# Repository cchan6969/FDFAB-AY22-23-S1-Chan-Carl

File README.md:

# FDFAB-AY22-23-S1-Chan-Carl

Project Webpage + Repository for the Elective Module Further Digital Fabrication and Prototyping Fundementals.

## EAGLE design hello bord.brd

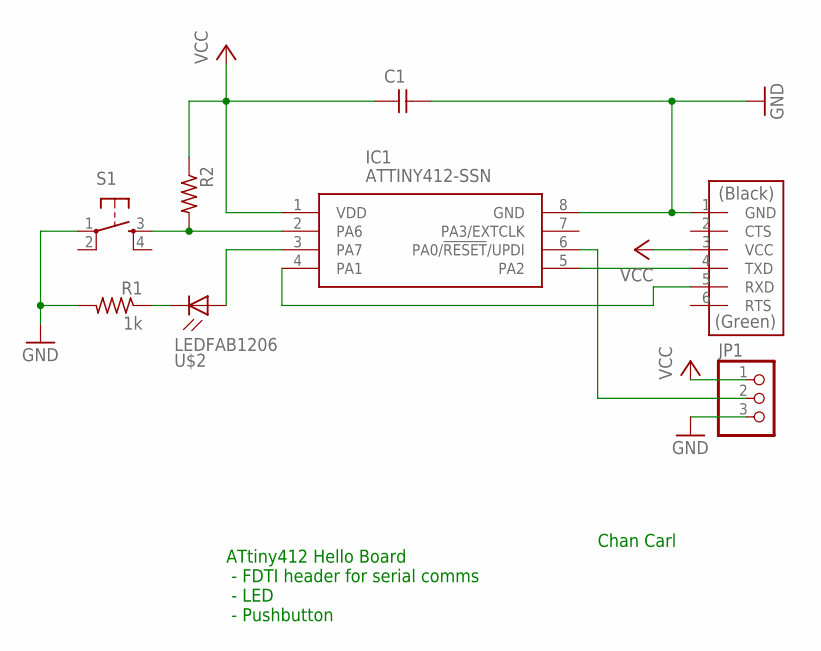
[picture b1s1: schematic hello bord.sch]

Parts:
C1: CAP_UNPOLARIZED; C1206
IC1: ATTINY412-SSN; SOIC127P600X175-8N
JP1: PINHD-1X3; 1X03
R1: 1k; R1206
R2: R1206
S1: SW_SWITCH_TACTILE_6MM6MM_SWITCH; 6MM_SWITCH
U$1: CONN_06_FTDI-SMD-HEADER; 1X06SMD
U$2: LEDFAB1206; LED1206FAB

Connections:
GND: C1.2, IC1.8 (GND), JP1.3, R1.2, S1.1, U$1.1 (GND)
unnamed: IC1.6 (PA0/!RESET!/UPDI), JP1.2
unnamed: IC1.3 (PA7), U$2.1 (A)
unnamed: R1.1, U$2.2 (C)
unnamed: IC1.5 (PA2), U$1.4 (TXD)
unnamed: IC1.4 (PA1), U$1.5 (RXD)
unnamed: IC1.2 (PA6), R2.2, S1.3 (S)
VCC: C1.1, IC1.1 (VDD), JP1.1, R2.1, U$1.3 (VCC)

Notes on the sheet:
Chan Carl
ATtiny412 Hello Board - FDTI header for serial comms - LED - Pushbutton

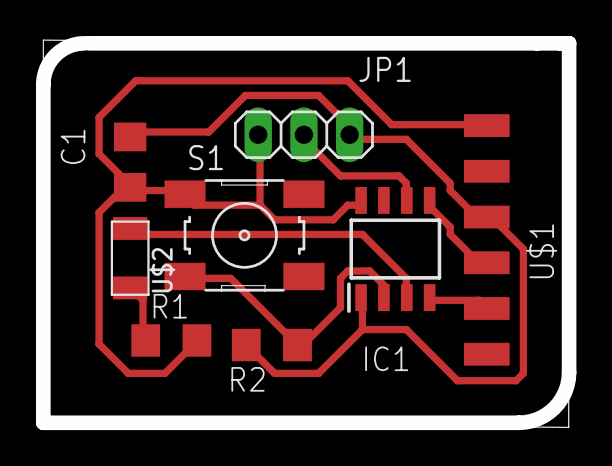
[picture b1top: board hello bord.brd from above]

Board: 2 copper layers, 29.2 x 21.1 mm, 8 parts (0 on the bottom side), 8 nets.

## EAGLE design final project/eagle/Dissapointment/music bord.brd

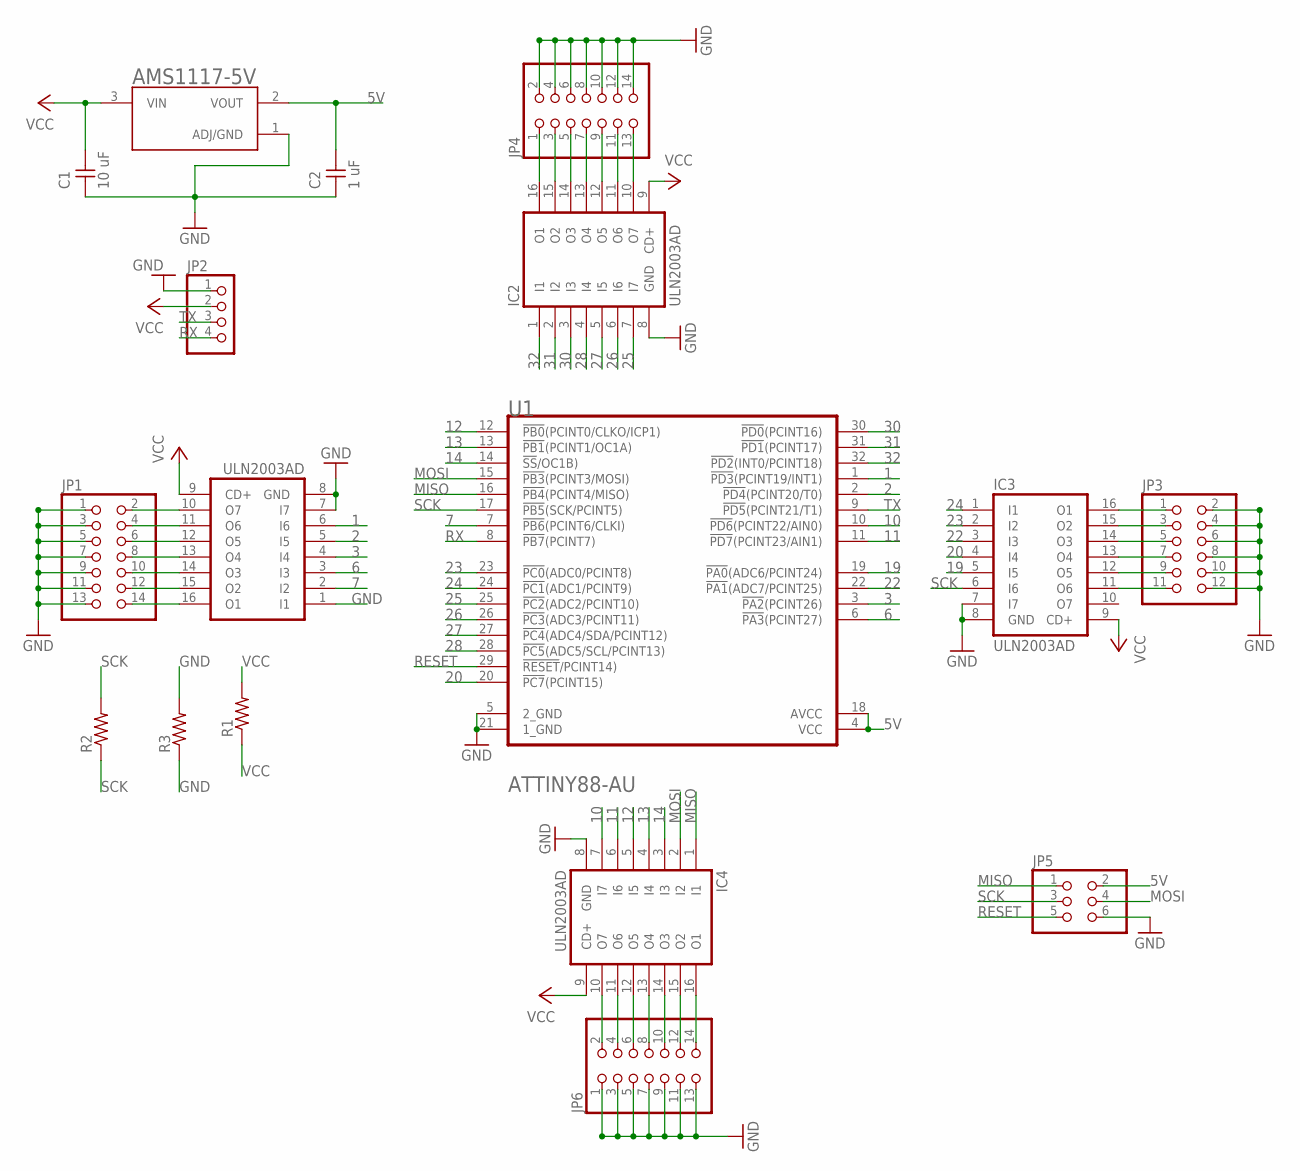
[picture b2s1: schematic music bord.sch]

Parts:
AMS1117-5V: AMS1117-3.3; SOT229P700X180-4N
C1: 10 uF; C1206FAB
C2: 1 uF; C1206FAB
IC1, IC2, IC3, IC4: ULN2003AD; SO16
JP1, JP4, JP6: PINHD-2X7SMT; 2X07_SMT
JP2: PINHD-1X4/90; 1X04/90
JP3: PINHD-2X6SMT; 2X06_SMT
JP5: CONN_03X2-PINHEAD-SMD; 2X03SMD
R1, R2, R3: R1206FAB
U1: MICROCHIP_-_ATMEL_ATTINY88-AUMICROCHIP_-_ATMEL_AT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; MICROCHIP_-_ATMEL_ATTINY88-AU_0

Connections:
1: IC1.6 (I6), U1.1 (!PD3!(PCINT19/INT1))
2: IC1.5 (I5), U1.2 (!PD4!(PCINT20/T0))
3: IC1.4 (I4), U1.3 (!PA2!(PCINT26))
5V: AMS1117-5V.2 (VOUT), C2.2, JP5.2, U1.4 (VCC), U1.18 (AVCC)
6: IC1.3 (I3), U1.6 (!PA3!(PCINT27))
7: IC1.2 (I2), U1.7 (!PB6!(PCINT6/CLKI))
10: IC4.7 (I7), U1.10 (!PD6!(PCINT22/AIN0))
11: IC4.6 (I6), U1.11 (!PD7!(PCINT23/AIN1))
12: IC4.5 (I5), U1.12 (!PB0!(PCINT0/CLKO/ICP1))
13: IC4.4 (I4), U1.13 (!PB1!(PCINT1/OC1A))
14: IC4.3 (I3), U1.14 (!SS!/OC1B))
19: IC3.5 (I5), U1.19 (!PA0!(ADC6/PCINT24))
20: IC3.4 (I4), U1.20 (!PC7!(PCINT15))
22: IC3.3 (I3), U1.22 (!PA1!(ADC7/PCINT25))
23: IC3.2 (I2), U1.23 (!PC0!(ADC0/PCINT8))
24: IC3.1 (I1), U1.24 (!PC1!(ADC1/PCINT9))
25: IC2.7 (I7), U1.25 (!PC2!(ADC2/PCINT10))
26: IC2.6 (I6), U1.26 (!PC3!(ADC3/PCINT11))
27: IC2.5 (I5), U1.27 (!PC4!(ADC4/SDA/PCINT12))
28: IC2.4 (I4), U1.28 (!PC5!(ADC5/SCL/PCINT13))
30: IC2.3 (I3), U1.30 (!PD0!(PCINT16))
31: IC2.2 (I2), U1.31 (!PD1!(PCINT17))
32: IC2.1 (I1), U1.32 (!PD2!(INT0/PCINT18))
GND: AMS1117-5V.1 (ADJ/GND), C1.1, C2.1, IC1.1 (I1), IC1.7 (I7), IC1.8 (GND), IC2.8 (GND), IC3.7 (I7), IC3.8 (GND), IC4.8 (GND), JP1.1, JP1.3, JP1.5, JP1.7, JP1.9, JP1.11, JP1.13, JP2.1, JP3.2, JP3.4, JP3.6, JP3.8, JP3.10, JP3.12, JP4.2, JP4.4, JP4.6, JP4.8, JP4.10, JP4.12, JP4.14, JP5.6, JP6.1, JP6.3, JP6.5, JP6.7, JP6.9, JP6.11, JP6.13, R3.1, R3.2, U1.5 (2_GND), U1.21 (1_GND)
MISO: IC4.1 (I1), JP5.1, U1.16 (!PB4!(PCINT4/MISO))
MOSI: IC4.2 (I2), JP5.4, U1.15 (!PB3!(PCINT3/MOSI))
unnamed: IC1.10 (O7), JP1.2
unnamed: IC4.10 (O7), JP6.2
unnamed: IC4.11 (O6), JP6.4
unnamed: IC4.12 (O5), JP6.6
unnamed: IC4.13 (O4), JP6.8
unnamed: IC4.14 (O3), JP6.10
unnamed: IC4.15 (O2), JP6.12
unnamed: IC4.16 (O1), JP6.14
unnamed: IC1.16 (O1), JP1.14
unnamed: IC3.16 (O1), JP3.1
unnamed: IC3.15 (O2), JP3.3
unnamed: IC3.14 (O3), JP3.5
unnamed: IC3.13 (O4), JP3.7
unnamed: IC3.12 (O5), JP3.9
unnamed: IC3.11 (O6), JP3.11
unnamed: IC2.16 (O1), JP4.1
unnamed: IC2.15 (O2), JP4.3
unnamed: IC2.14 (O3), JP4.5
unnamed: IC2.13 (O4), JP4.7
unnamed: IC2.12 (O5), JP4.9
unnamed: IC2.11 (O6), JP4.11
unnamed: IC2.10 (O7), JP4.13
unnamed: IC1.11 (O6), JP1.4
unnamed: IC1.12 (O5), JP1.6
unnamed: IC1.13 (O4), JP1.8
unnamed: IC1.14 (O3), JP1.10
unnamed: IC1.15 (O2), JP1.12
RESET: JP5.5, U1.29 (!RESET!/PCINT14))
RX: JP2.4, U1.8 (!PB7!(PCINT7))
SCK: IC3.6 (I6), JP5.3, R2.1, R2.2, U1.17 (!PB5!(SCK/PCINT5))
TX: JP2.3, U1.9 (!PD5!(PCINT21/T1))
VCC: AMS1117-5V.3 (VIN), C1.2, IC1.9 (CD+), IC2.9 (CD+), IC3.9 (CD+), IC4.9 (CD+), JP2.2, R1.1, R1.2

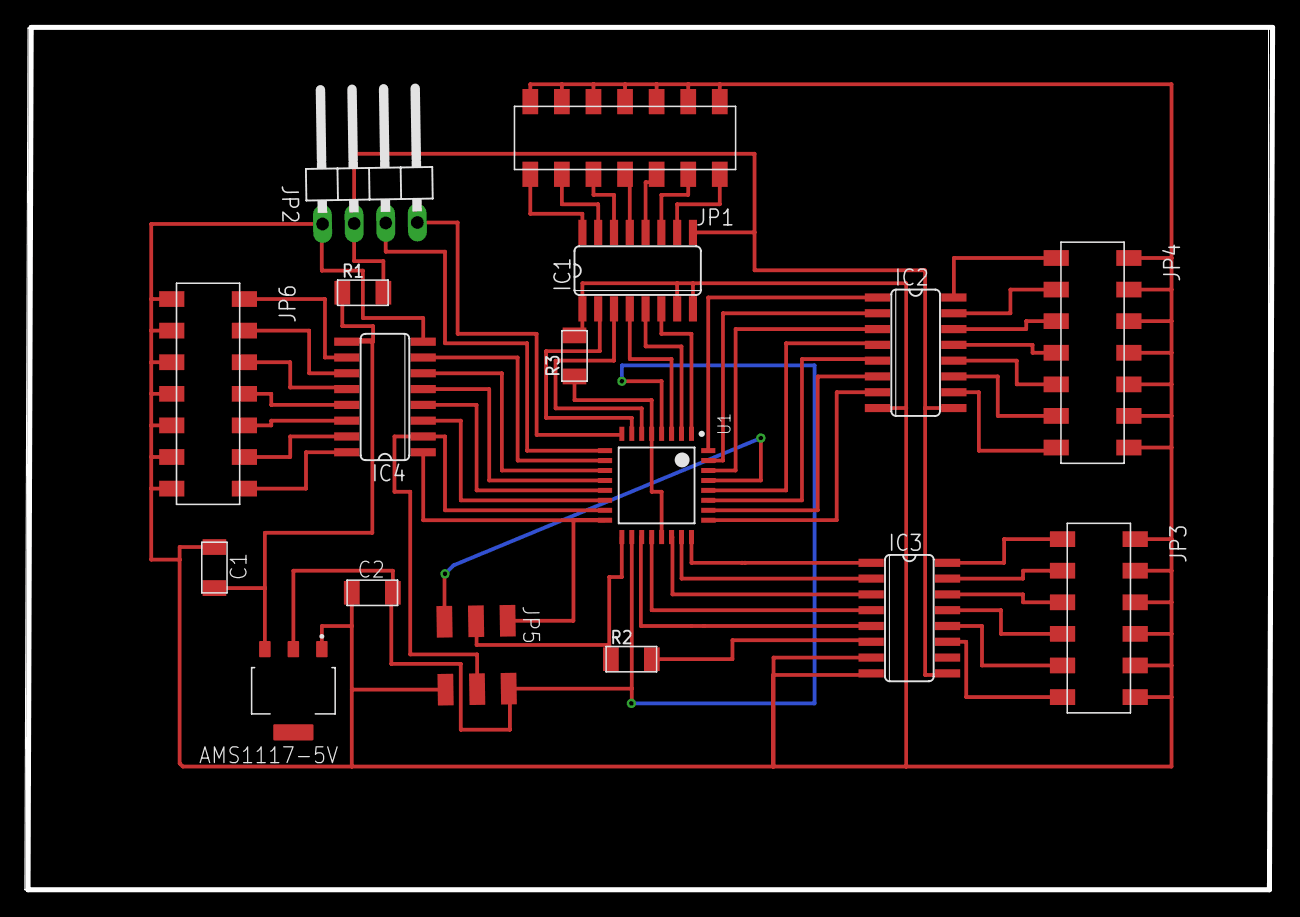
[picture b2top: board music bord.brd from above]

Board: 2 copper layers, 100.1 x 69.3 mm, 17 parts (0 on the bottom side), 58 nets.

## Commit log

2022-04-22 using old EP1000 website skeleton
2022-04-22 updating nav bar and adding agreement
2022-04-25 learning Java for RIP
2022-05-20 CLC Python Course
2022-06-16 Add in pcb.html
2022-06-24 add pics into website pcb.html
2022-07-02 move pictures to folder
2022-07-02 add memes
2022-07-02 include cnc.html
2022-07-02 update the png directry
2022-07-03 Update pcb.html
    add details on 1st 2 board plus specs of hello board
2022-07-03 forgot .png
2022-07-03 add images
2022-07-03 Update pcb.html
    IMAGINE USING 2 DIFFERENT FILE FORMATS
2022-07-03 how to solder
    fuji vs ice cream
2022-07-03 recenter img on pcb.html
2022-07-03 update nav bar
2022-07-03 Update pcb.html
    increase img size
2022-07-03 update pcb process
2022-07-03 update mods instructions
2022-07-03 Update pcb.html
    deleted extra w
2022-07-03 Update ftdi.jpg
    rotate the image
2022-07-03 Create Hello wrong.png
    image of terrible soldering
2022-07-03 pics ot auto route
2022-07-03 hello board nc
2022-07-03 Update pcb.html
    add link to mt fuji photo
2022-08-22 update pcb and music bord v1
2022-08-25 pcb eagle pngs
2022-08-25 put in eagle porject
2022-08-27 create new folder for cnc photos
2022-08-27 images
2022-08-27 new pages + edit nav bar
2022-08-27 remove text
2022-08-28 change name of resin mould casting to resin casting
2022-08-28 adding images
    for resin mould and cnc coaster
2022-08-28 and <code>
2022-08-28 added <pre>
2022-08-28 Update cnc.html
    include embeded link for flat pack
2022-08-28 Update resin.html
    embeaded link for resin mould fusion 360
2022-08-28 add pic
2022-08-31 import images
2022-08-31 new lbr libraries
2022-08-31 Create ali trace.png
    trace for new board
2022-08-31 Update Fcode.html
    insert code for music, mary had a little lamb
2022-08-31 add more pictures
2022-09-01 find images
2022-09-01 media for final video
2022-09-01 presentation vid
